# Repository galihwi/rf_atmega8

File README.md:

# RF communication with ATmega8

Files:
- Receiver source code for ATmega8
- PCB schematic for receiver and transmitter module

Team:
- Ahmad Ishtar Terra

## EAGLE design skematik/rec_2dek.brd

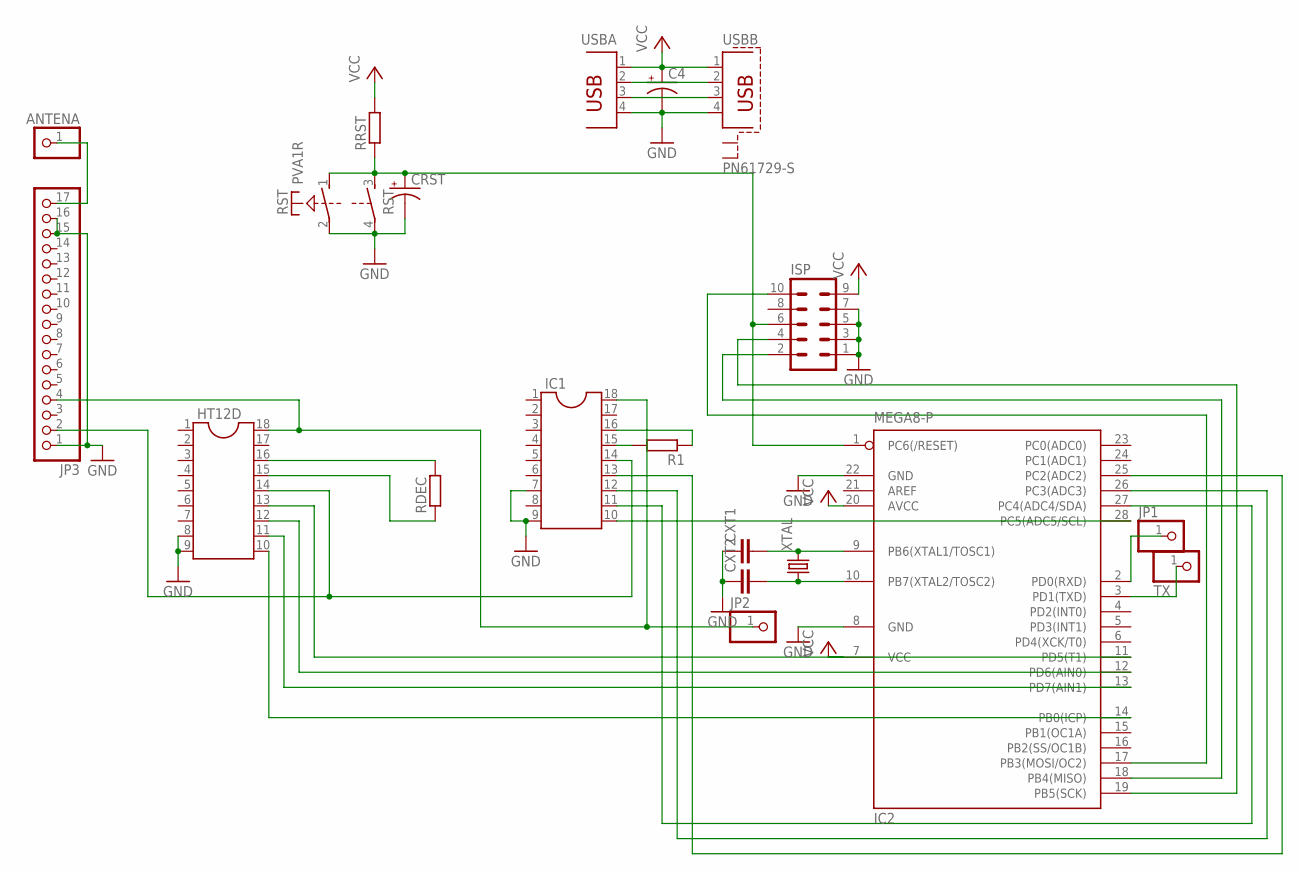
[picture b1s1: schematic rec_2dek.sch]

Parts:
ANTENA: PINHD-1X1; 1X01
C4: CPOL-USE2.5-7; E2,5-7
CRST: CPOL-USE2.5-7; E2,5-7
CXT1, CXT2: C2.5/2; C2.5-2
HT12D: DIL18S; SOCKET-18
IC1: DIL18S; SOCKET-18
IC2: MEGA8-P; DIL28-3
ISP: MA05-2
JP1, JP2: PINHD-1X1; 1X01
JP3: PINHD-1X17; 1X17
R1: R-EU_0207/12; 0207/12
RDEC: R-EU_0309/12; 0309/12
RRST: R-EU_0207/10; 0207/10
RST: PVA1R
TX: PINHD-1X1; 1X01
USBA: PN87520
USBB: PN61729-S
XTAL: CRYSTALHC49S; HC49/S

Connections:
GND: C4.-, CRST.-, CXT1.1, CXT2.1, HT12D.8, HT12D.9, IC1.7, IC1.9, IC2.8 (GND), IC2.22 (GND), ISP.1, ISP.3, ISP.5, ISP.7, JP3.1, JP3.15, JP3.16, RST.2, RST.4, USBA.4, USBB.4
unnamed: CXT1.2, IC2.9 (PB6(XTAL1/TOSC1)), XTAL.2
unnamed: CXT2.2, IC2.10 (PB7(XTAL2/TOSC2)), XTAL.1
unnamed: IC2.3 (PD1(TXD)), TX.1
unnamed: IC2.19 (PB5(SCK)), ISP.4
unnamed: IC2.17 (PB3(MOSI/OC2)), ISP.10
unnamed: ANTENA.1, JP3.17
unnamed: IC2.18 (PB4(MISO)), ISP.2
unnamed: CRST.+, IC2.1 (PC6(/RESET)), ISP.6, RRST.1, RST.1 (S), RST.3 (S)
unnamed: USBA.2, USBB.2
unnamed: USBA.3, USBB.3
unnamed: HT12D.10, IC2.14 (PB0(ICP))
unnamed: HT12D.11, IC2.13 (PD7(AIN1))
unnamed: HT12D.12, IC2.12 (PD6(AIN0))
unnamed: HT12D.13, IC2.11 (PD5(T1))
unnamed: HT12D.16, RDEC.2
unnamed: HT12D.15, RDEC.1
unnamed: HT12D.14, IC1.14, JP3.2
unnamed: IC1.15, R1.2
unnamed: HT12D.18, IC1.18, JP2.1, JP3.4
unnamed: IC1.16, R1.1
unnamed: IC1.10, IC2.28 (PC5(ADC5/SCL))
unnamed: IC1.11, IC2.27 (PC4(ADC4/SDA))
unnamed: IC1.12, IC2.26 (PC3(ADC3))
unnamed: IC1.13, IC2.25 (PC2(ADC2))
unnamed: IC2.2 (PD0(RXD)), JP1.1
VCC: C4.+, IC2.7 (VCC), IC2.20 (AVCC), ISP.9, RRST.2, USBA.1, USBB.1

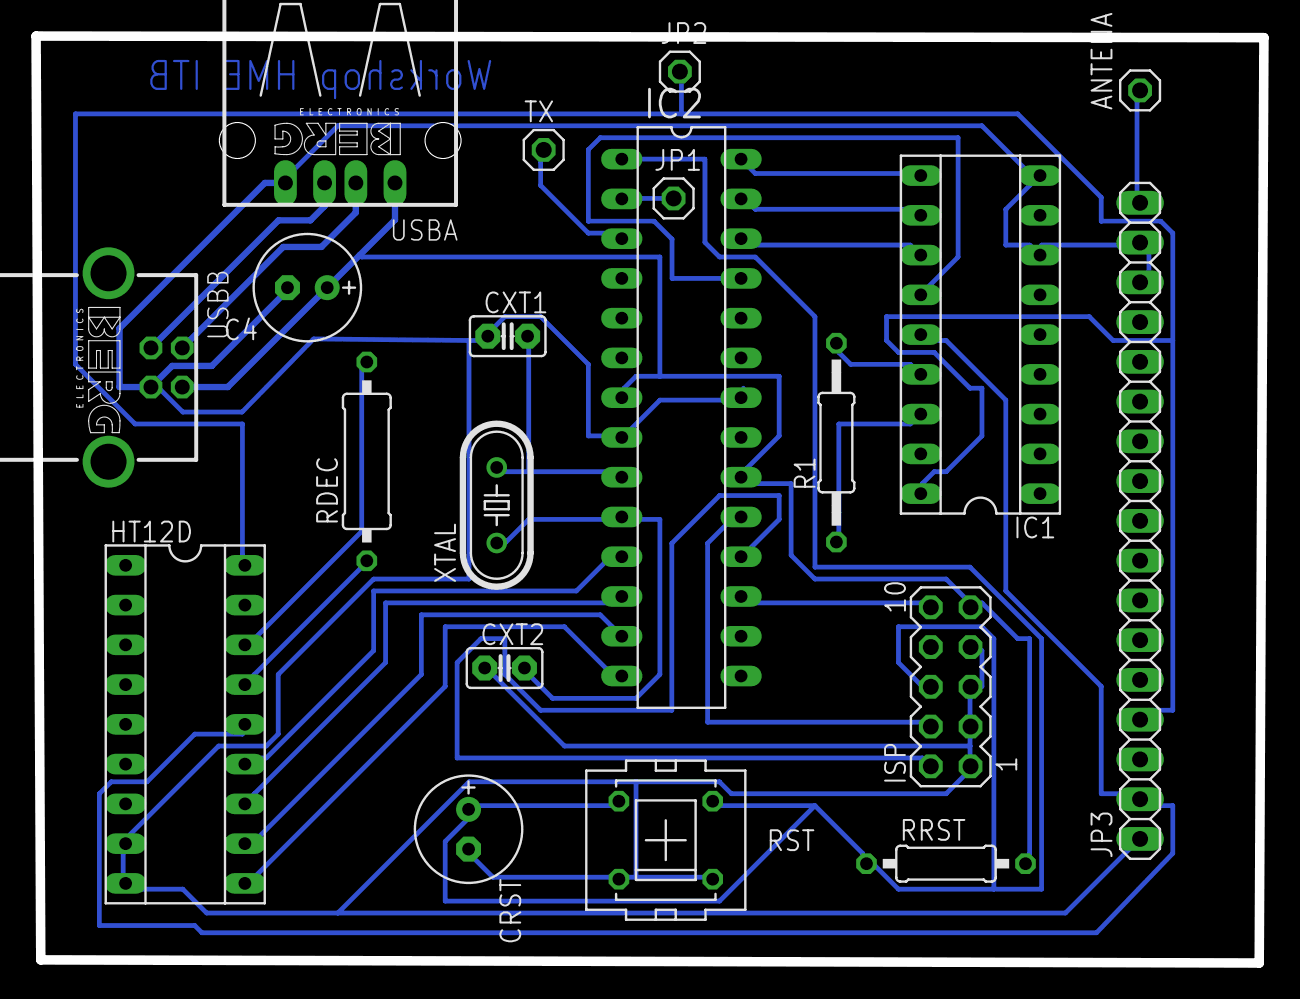
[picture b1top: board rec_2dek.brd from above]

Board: 2 copper layers, 78.4 x 59.2 mm, 20 parts (0 on the bottom side), 27 nets.

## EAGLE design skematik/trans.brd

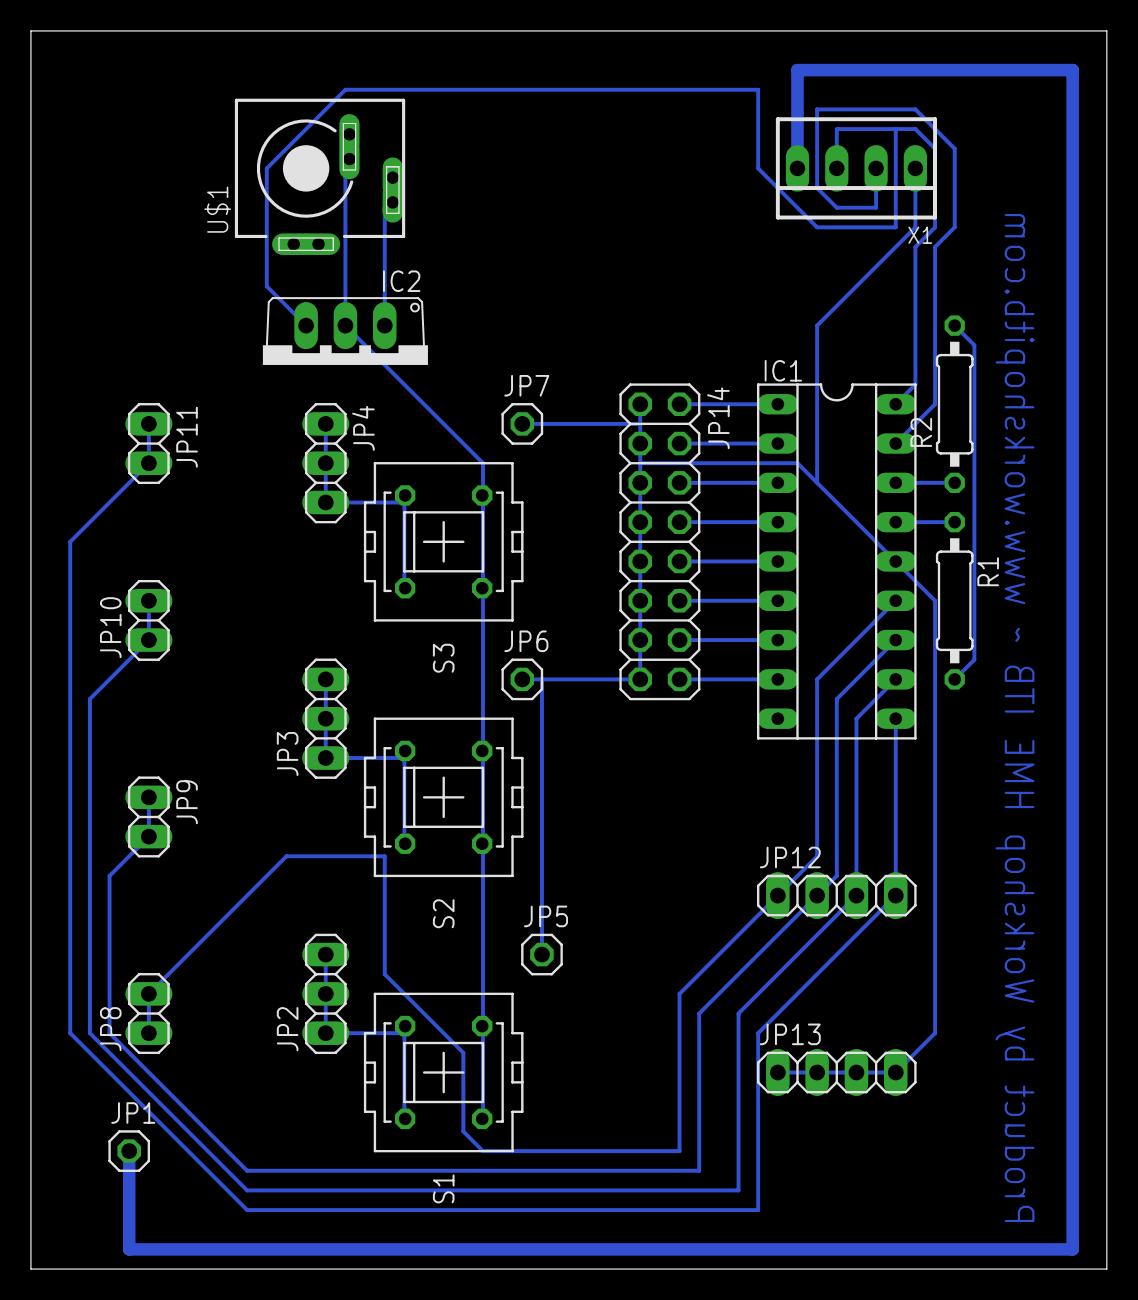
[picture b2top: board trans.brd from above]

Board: 2 copper layers, 69.5 x 80.0 mm, 23 parts (0 on the bottom side), 24 nets.

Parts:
IC1: SOCKET-18
IC2: 7805TV; TO220V
JP1, JP5, JP6, JP7: 1X01
JP2, JP3, JP4: 1X03
JP8, JP9, JP10, JP11: 1X02
JP12, JP13: 1X04
JP14: 2X08
R1, R2: 0207/10
S1, S2, S3: PVA1R
U$1: KLDVX-0202-C
X1: 22-23-2041

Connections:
unnamed: IC1.14, JP5.1, JP6.1, JP7.1, JP13.1, JP13.2, JP13.3, JP13.4, JP14.1, JP14.3, JP14.5, JP14.7, JP14.9, JP14.11, JP14.13, JP14.15, X1.1
unnamed: IC1.10, JP11.1, JP11.2, JP12.4
unnamed: IC1.11, JP10.1, JP10.2, JP12.3
unnamed: IC1.12, JP9.1, JP9.2, JP12.2
unnamed: IC1.13, JP8.1, JP8.2, JP12.1
unnamed: JP2.1, JP2.2, JP2.3, S1.2, S1.4
unnamed: IC2.1, U$1.2
unnamed: JP3.1, JP3.2, JP3.3, S2.2, S2.4
unnamed: IC1.15, R1.1
unnamed: IC1.16, R2.1
unnamed: R1.2, R2.2
unnamed: JP4.1, JP4.2, JP4.3, S3.2, S3.4
unnamed: IC1.17, X1.2
unnamed: JP1.1, X1.4
unnamed: IC2.2, S1.1, S1.3, S2.1, S2.3, S3.1, S3.3, U$1.3
unnamed: IC1.1, JP14.2
unnamed: IC1.2, JP14.4
unnamed: IC1.3, JP14.6
unnamed: IC1.4, JP14.8
unnamed: IC1.5, JP14.10
unnamed: IC1.6, JP14.12
unnamed: IC1.7, JP14.14
unnamed: IC1.8, JP14.16
VCC: IC1.18, IC2.3, X1.3
